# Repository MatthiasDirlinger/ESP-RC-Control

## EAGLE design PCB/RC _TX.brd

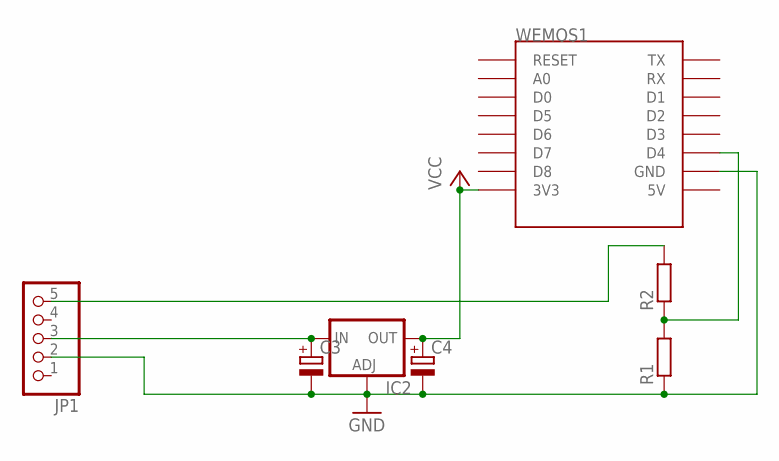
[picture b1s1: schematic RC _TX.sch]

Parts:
C3, C4: CPOL-EUE2,5-6E; E2,5-6E
IC2: LM317TS; 317TS
JP1: PINHD-1X5; 1X05
R1, R2: R-EU_0207/10; 0207/10
WEMOS1: WEMOS-D1-MINI

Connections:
GND: C3.-, C4.-, IC2.1 (ADJ), JP1.2, R1.1, WEMOS1.GND
unnamed: C3.+, IC2.3 (IN), JP1.3
unnamed: R1.2, R2.1, WEMOS1.D4
unnamed: JP1.5, R2.2
VCC: C4.+, IC2.2 (OUT), WEMOS1.3V3

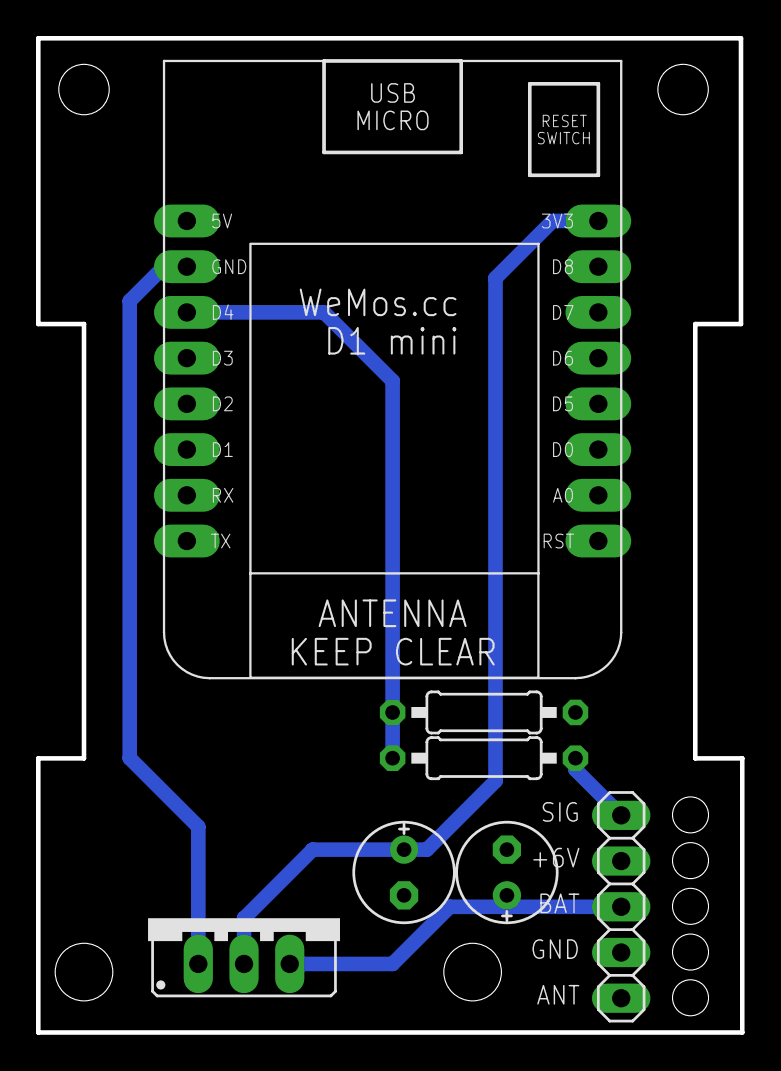
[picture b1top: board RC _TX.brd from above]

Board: 2 copper layers, 39.1 x 55.2 mm, 7 parts (0 on the bottom side), 5 nets.

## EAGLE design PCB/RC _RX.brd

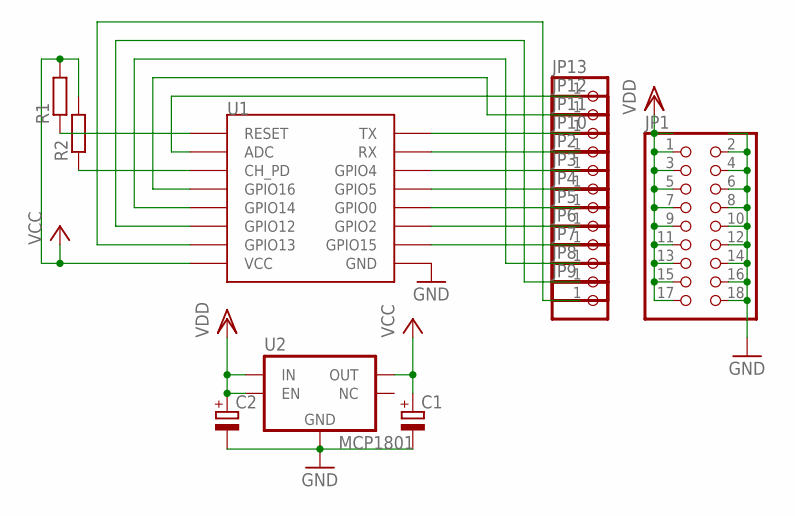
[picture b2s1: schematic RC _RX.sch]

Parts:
C1, C2: CPOL-EUA/3216-18W; A/3216-18W
JP1: PINHD-2X9; 2X09
JP2, JP3, JP4, JP5, JP6, JP7, JP8, JP9, JP10, JP11, JP12, JP13: PINHD-1X1; 1X01
R1, R2: R-EU_R0805; R0805
U1: ESP12
U2: MCP1801; SOT23-5

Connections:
GND: C1.-, C2.-, JP1.2, JP1.4, JP1.6, JP1.8, JP1.10, JP1.12, JP1.14, JP1.16, JP1.18, U1.GND, U2.2 (GND)
unnamed: R1.1, U1.RESET
unnamed: JP11.1, U1.TX
unnamed: JP2.1, U1.GPIO4
unnamed: JP3.1, U1.GPIO5
unnamed: JP4.1, U1.GPIO0
unnamed: JP5.1, U1.GPIO2
unnamed: JP6.1, U1.GPIO15
unnamed: JP7.1, U1.GPIO14
unnamed: JP8.1, U1.GPIO12
unnamed: JP9.1, U1.GPIO13
unnamed: JP10.1, U1.RX
unnamed: R2.1, U1.CH_PD
unnamed: JP12.1, U1.GPIO16
unnamed: JP13.1, U1.ADC
VCC: C1.+, R1.2, R2.2, U1.VCC, U2.5 (OUT)
VDD: C2.+, JP1.1, JP1.3, JP1.5, JP1.7, JP1.9, JP1.11, JP1.13, JP1.15, JP1.17, U2.1 (IN), U2.3 (EN)

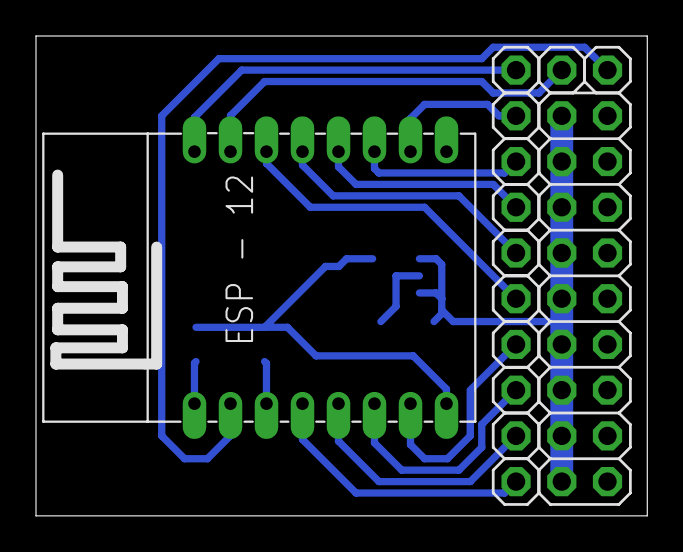
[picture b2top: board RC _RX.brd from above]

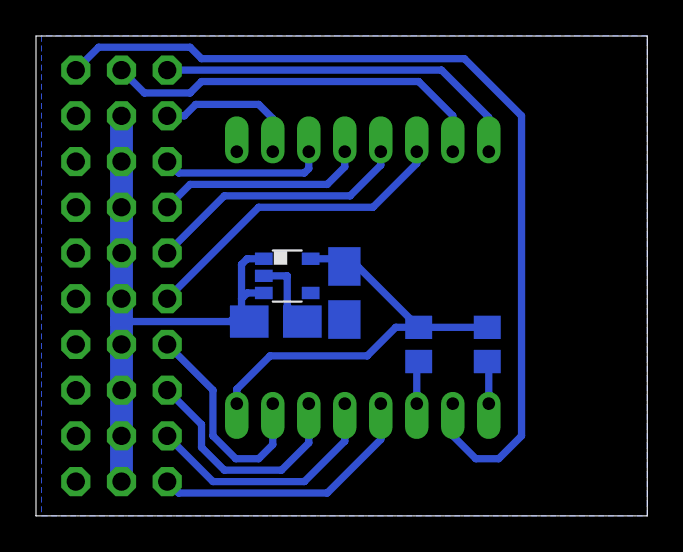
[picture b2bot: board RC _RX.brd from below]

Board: 2 copper layers, 34.0 x 26.7 mm, 19 parts (5 on the bottom side), 17 nets.
